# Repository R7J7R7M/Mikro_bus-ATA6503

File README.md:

# ATA6503 MikroBUS Transceiver

## Introduction
The **ATA6503 MikroBUS** module is designed to convert standard **CAN TX** and **CAN RX** lines into **CANL** and **CANH** lines. It uses the **ATA6503** IC, securely mounted on a custom PCB. This module is extremely useful for CAN protocol-based projects where an external transceiver is required.  
For more technical specifications, please refer to the **Features** section below.

---

## Features
- **Voltage Compatibility**: Supports operation at both **3.3V** and **5V**. (A **3.3V LDO** is used for voltage conversion.)
- **Wake-Up Button**: Easily wake the device from sleep mode.
- **Three-Color LEDs**: Status indicators for quick diagnostics.
- **DB9 Connector**: Standard DB9 port for CAN network connection.
- **Screwed Connectors**: Dedicated screw terminals for secure battery connection.

---

## Fabrication Notice
This device has **not yet been fabricated**.  
Before proceeding with PCB manufacturing, **please review the schematic carefully** to ensure all design requirements are met.

---

## Known Issues
- **Impedance Matching**:  
  Proper impedance matching (typically 120Ω termination resistors) has **not been incorporated** in the current design.  
  If your application requires strict impedance control, it is recommended to **add extra components** close to the **CANL** and **CANH** lines.

---

## Contact Information
- **Name**: Gokulrajaram A
- **Email**: gokulrajarama@gmail.com
- **Phone**: +91 90259 38745

---

## PCB Preview

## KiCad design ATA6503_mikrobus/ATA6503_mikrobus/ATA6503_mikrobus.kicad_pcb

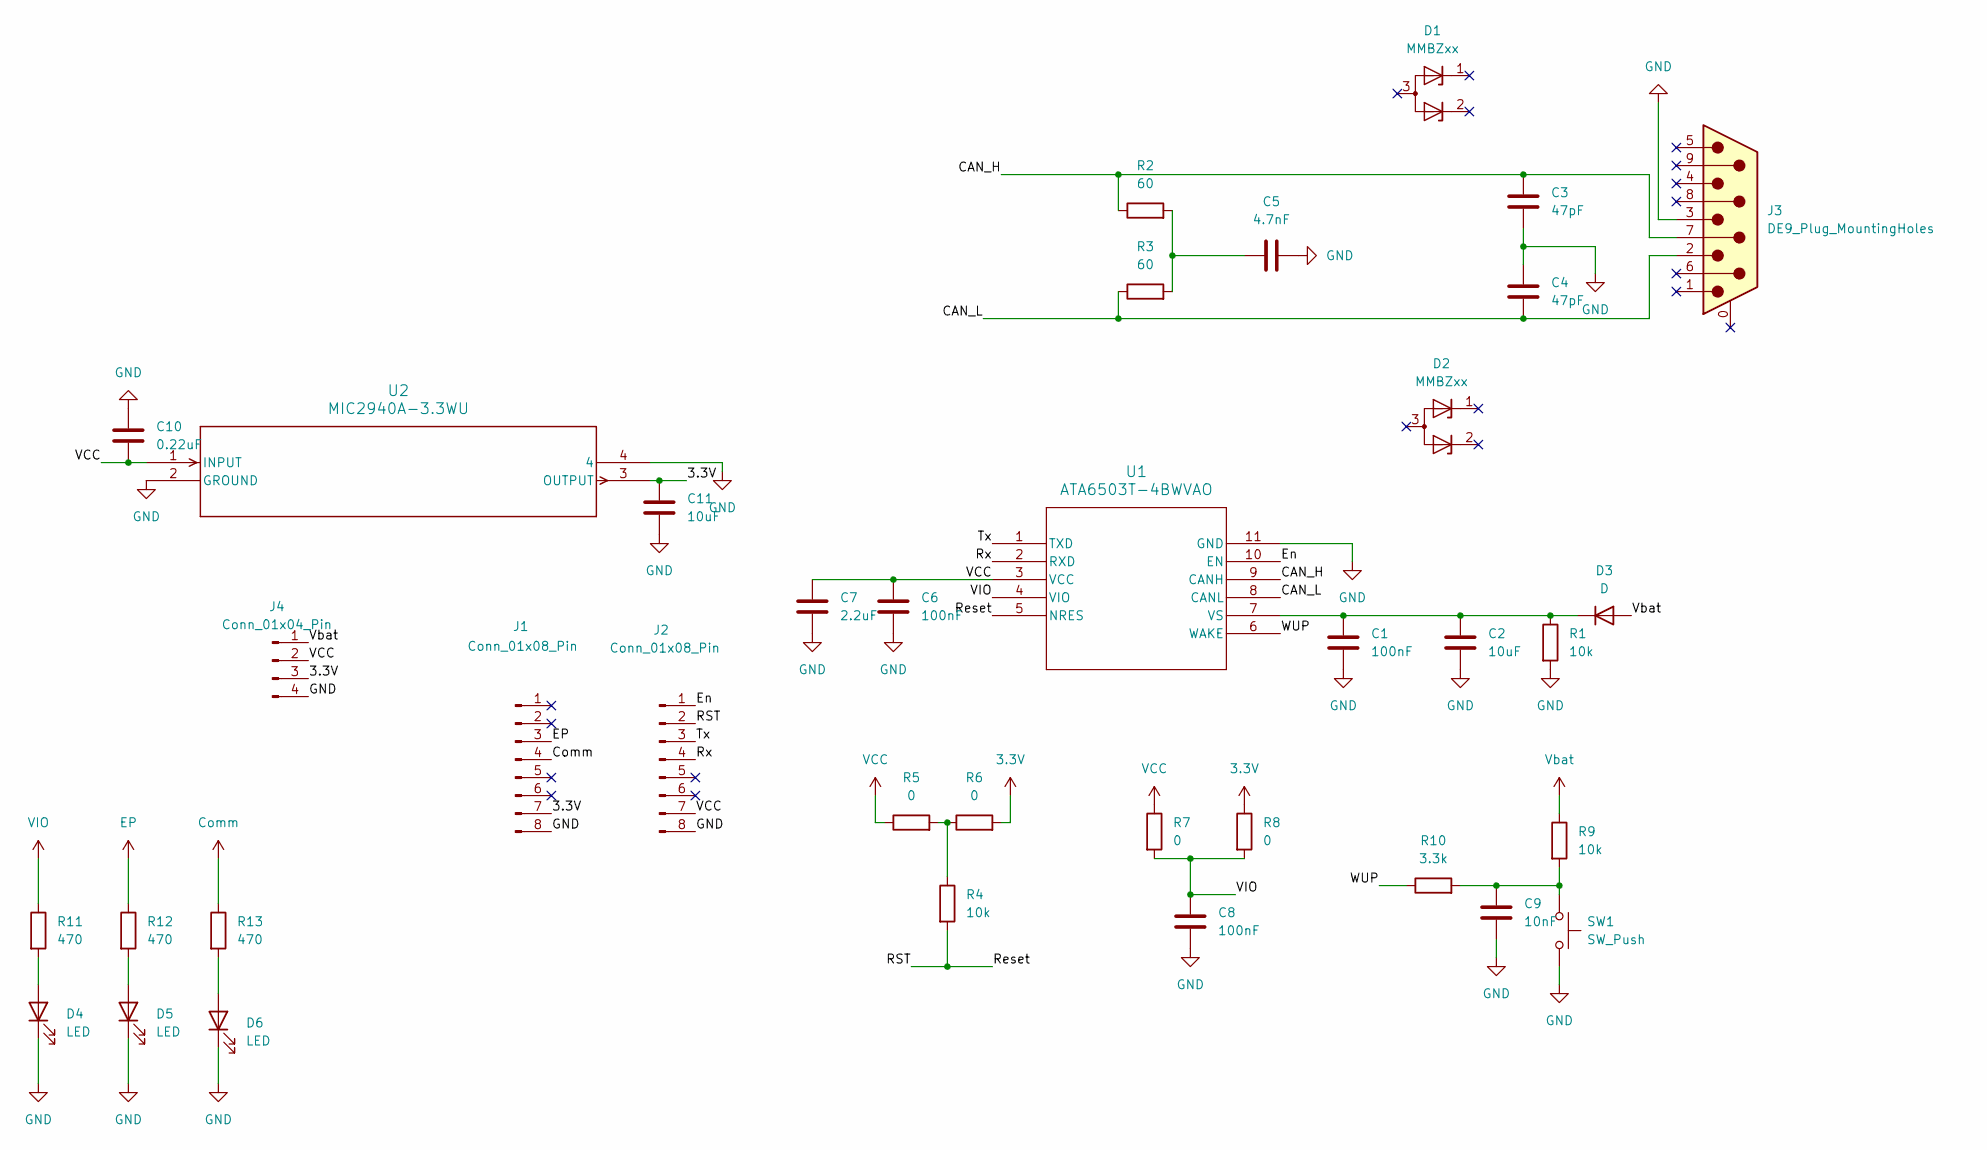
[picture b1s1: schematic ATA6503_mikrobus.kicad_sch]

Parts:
C1, C6, C8: 100nF; C_0805_2012Metric_Pad1.18x1.45mm_HandSolder
C2, C11: 10uF; C_0805_2012Metric_Pad1.18x1.45mm_HandSolder
C3, C4: 47pF; C_0805_2012Metric_Pad1.18x1.45mm_HandSolder
C5: 4.7nF; C_0805_2012Metric_Pad1.18x1.45mm_HandSolder
C7: 2.2uF; C_0805_2012Metric_Pad1.18x1.45mm_HandSolder
C9: 10nF; C_0805_2012Metric_Pad1.18x1.45mm_HandSolder
C10: 0.22uF; C_0805_2012Metric_Pad1.18x1.45mm_HandSolder
D1, D2: MMBZxx; SOT-23
D3: D; D_0805_2012Metric_Pad1.15x1.40mm_HandSolder
D4, D5, D6: LED; LED_0805_2012Metric_Pad1.15x1.40mm_HandSolder
J1, J2: Conn_01x08_Pin; PinHeader_1x08_P2.54mm_Vertical
J3: DE9_Plug_MountingHoles; DB9
J4: Conn_01x04_Pin; CONN4_500000G_AMP
R1, R4, R9: 10k; R_0805_2012Metric_Pad1.20x1.40mm_HandSolder
R2, R3: 60; R_0805_2012Metric_Pad1.20x1.40mm_HandSolder
R5, R6, R7, R8: 0; R_0805_2012Metric_Pad1.20x1.40mm_HandSolder
R10: 3.3k; R_0805_2012Metric_Pad1.20x1.40mm_HandSolder
R11, R12, R13: 470; R_0805_2012Metric_Pad1.20x1.40mm_HandSolder
SW1: SW_Push; SW_Push_1P1T_NO_6x6mm_H9.5mm
U1: ATA6503T-4BWVAO; VDFN10_4BW_2p3x1p7EP_MCH
U2: MIC2940A-3.3WU; TO263-3LD_MCH

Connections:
3.3V: C11.1, J1.7, J4.3, R6.2, R8.1, U2.3 (OUTPUT)
/CAN_H: C3.1, J3.7, R2.1, U1.9 (CANH)
/CAN_L: C4.2, J3.2, R3.1, U1.8 (CANL)
/En: J2.1, U1.10 (EN)
/RST: J2.2, R4.2, U1.5 (NRES)
/Rx: J2.4, U1.2 (RXD)
/Tx: J2.3, U1.1 (TXD)
/WUP: R10.1, U1.6 (WAKE)
Comm: J1.4, R13.1
EP: J1.3, R12.1
GND: C1.2, C2.2, C3.2, C4.1, C5.2, C6.2, C7.2, C8.2, C9.2, C10.2, C11.2, D4.1 (K), D5.1 (K), D6.1 (K), J1.8, J2.8, J3.3, J4.4, R1.2, SW1.2, U1.11 (GND), U2.2 (GROUND), U2.4
unnamed: C5.1, R2.2, R3.2
unnamed: C9.1, R9.2, R10.2, SW1.1
unnamed: C1.1, C2.1, D3.1 (K), R1.1, U1.7 (VS)
unnamed: D4.2 (A), R11.2
unnamed: D5.2 (A), R12.2
unnamed: D6.2 (A), R13.2
unnamed: R4.1, R5.2, R6.1
VCC: C6.1, C7.1, C10.1, J2.7, J4.2, R5.1, R7.1, U1.3 (VCC), U2.1 (INPUT)
VIO: C8.1, R7.2, R8.2, R11.1, U1.4 (VIO)
Vbat: D3.2 (A), J4.1, R9.1

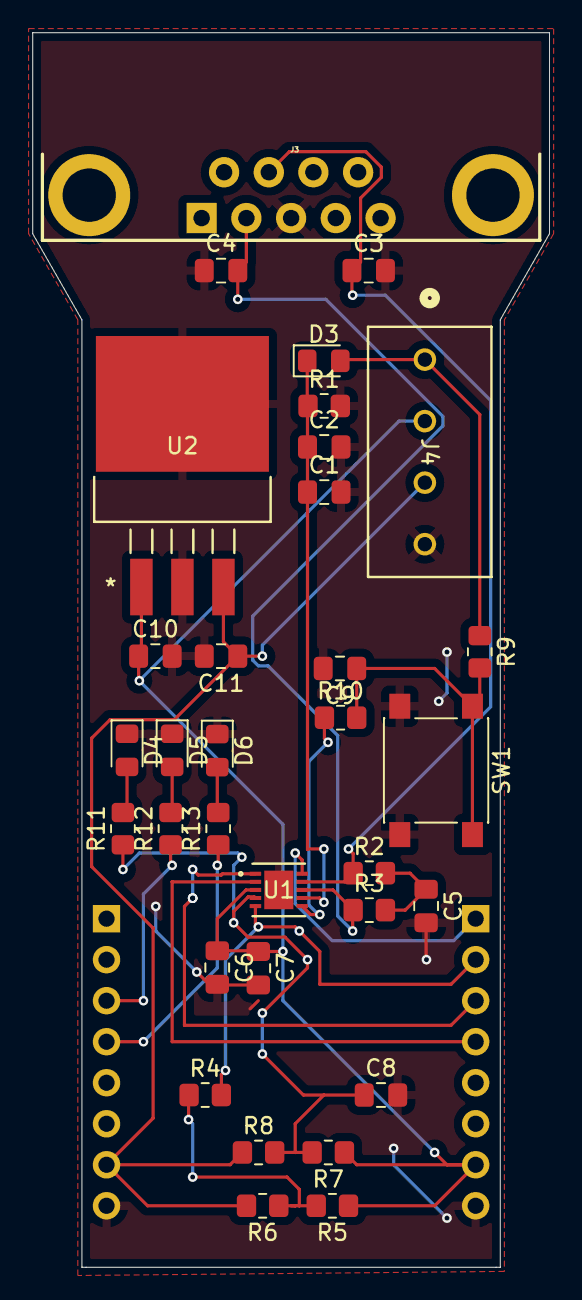
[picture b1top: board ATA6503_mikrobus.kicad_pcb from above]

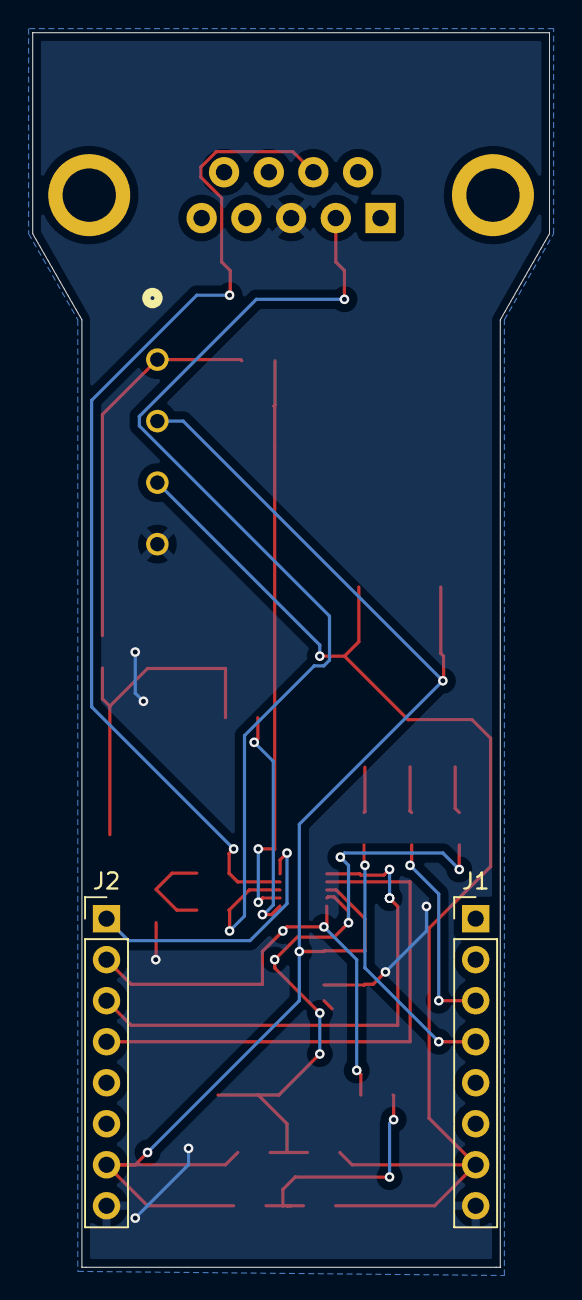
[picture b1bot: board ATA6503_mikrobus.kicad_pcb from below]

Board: 2 copper layers, 32.0 x 76.5 mm, 35 parts (2 on the bottom side), 21 nets.
